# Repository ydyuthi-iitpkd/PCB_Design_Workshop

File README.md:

# PCB_Design_Workshop
PCB Design Workshop Conducted by Y-Dyuthi Club IITPKD

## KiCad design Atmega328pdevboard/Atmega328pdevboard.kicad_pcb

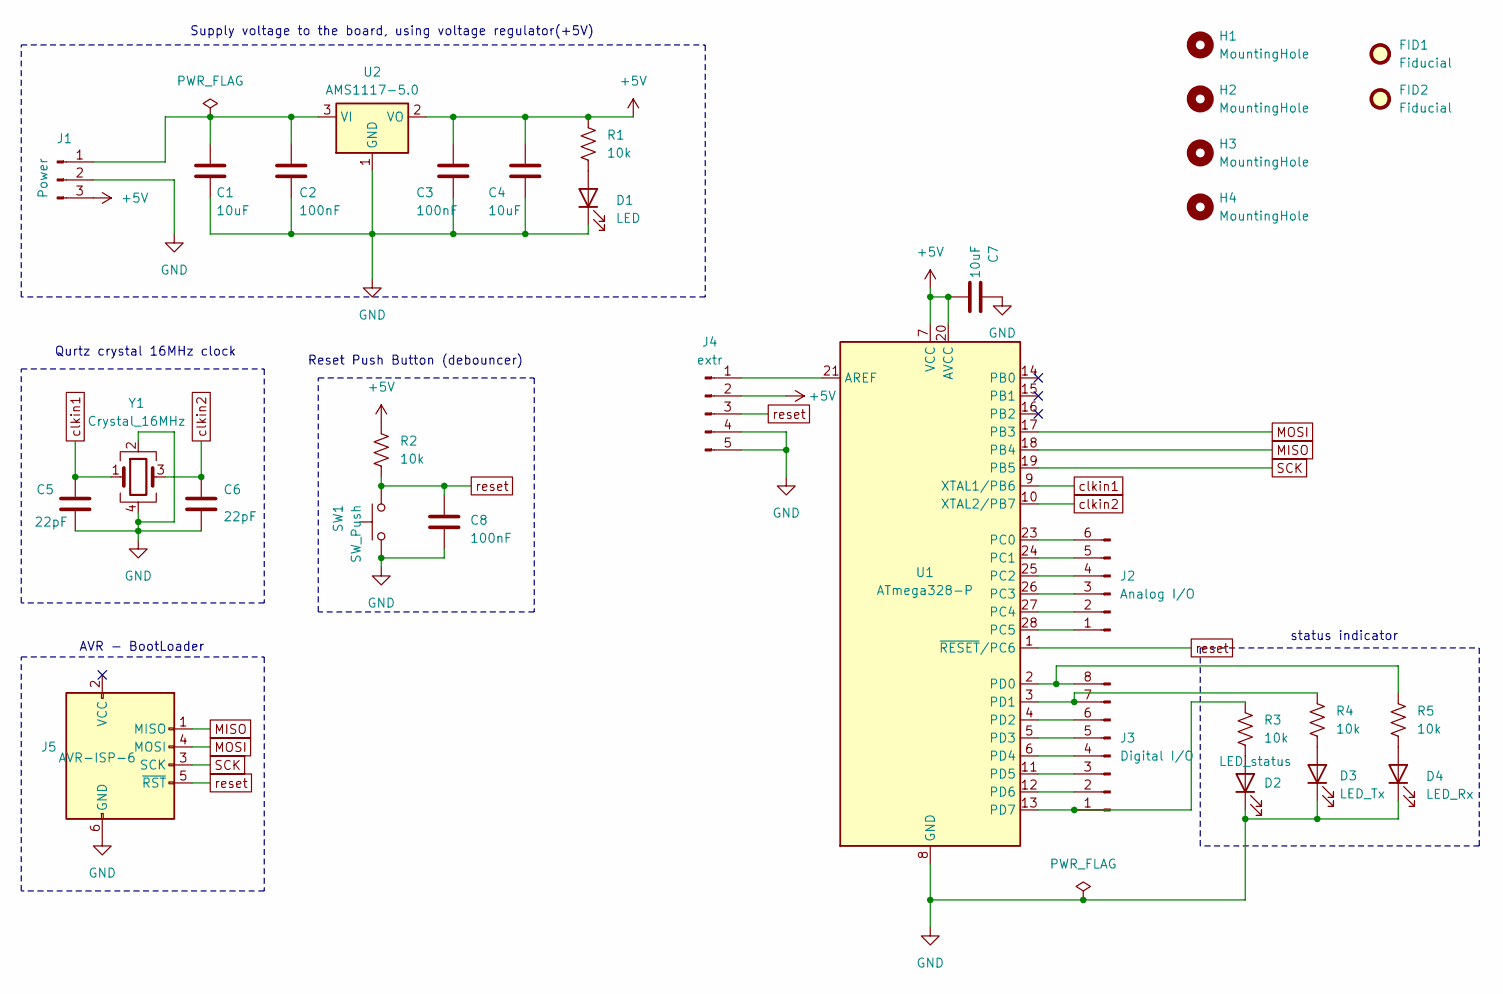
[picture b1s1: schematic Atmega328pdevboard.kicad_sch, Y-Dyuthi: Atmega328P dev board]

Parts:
C1, C4, C7: 10uF; C_0805_2012Metric
C2, C3, C8: 100nF; C_0805_2012Metric
C5, C6: 22pF; C_0402_1005Metric
D1: LED; LED_0805_2012Metric
D2: LED_status; LED_0805_2012Metric
D3: LED_Tx; LED_0805_2012Metric
D4: LED_Rx; LED_0805_2012Metric
FID1, FID2: Fiducial; Fiducial_0.5mm_Mask1.5mm
H1, H2, H3, H4: MountingHole; MountingHole_2.1mm
J1: Power; PinHeader_1x03_P1.27mm_Vertical
J2: Analog I/O; PinSocket_1x06_P1.27mm_Vertical
J3: Digital I/O; PinSocket_1x08_P1.27mm_Vertical
J4: extr; PinSocket_1x05_P1.27mm_Vertical
J5: AVR-ISP-6; PinHeader_2x03_P1.27mm_Vertical
R1, R2, R3, R4, R5: 10k; R_0805_2012Metric
SW1: SW_Push; SW_PUSH_6mm
U1: ATmega328-P; DIP-28_W7.62mm
U2: AMS1117-5.0; SOT-223-3_TabPin2
Y1: Crystal_16MHz; Crystal_SMD_0603-4Pin_6.0x3.5mm

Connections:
+5V: C3.1, C4.1, C7.2, J1.3, J4.2, R1.2, R2.2, U1.7 (VCC), U1.20 (AVCC), U2.2 (VO)
GND: C1.2, C2.2, C3.2, C4.2, C5.2, C6.2, C7.1, C8.2, D1.1 (K), D2.1 (K), D3.1 (K), D4.1 (K), J1.2, J4.4, J4.5, J5.6 (GND), SW1.1, U1.8 (GND), U1.22 (GND), U2.1 (GND), Y1.2, Y1.4
MISO: J5.1 (MISO), U1.18 (PB4)
MOSI: J5.4 (MOSI), U1.17 (PB3)
unnamed: D1.2 (A), R1.1
unnamed: D2.2 (A), R3.1
unnamed: D3.2 (A), R4.1
unnamed: D4.2 (A), R5.1
unnamed: C1.1, C2.1, J1.1, U2.3 (VI)
unnamed: J2.1, U1.28 (PC5)
unnamed: J2.2, U1.27 (PC4)
unnamed: J2.3, U1.26 (PC3)
unnamed: J2.4, U1.25 (PC2)
unnamed: J2.5, U1.24 (PC1)
unnamed: J2.6, U1.23 (PC0)
unnamed: J3.1, R3.2, U1.13 (PD7)
unnamed: J3.2, U1.12 (PD6)
unnamed: J3.3, U1.11 (PD5)
unnamed: J3.4, U1.6 (PD4)
unnamed: J3.5, U1.5 (PD3)
unnamed: J3.6, U1.4 (PD2)
unnamed: J3.7, R4.2, U1.3 (PD1)
unnamed: J3.8, R5.2, U1.2 (PD0)
unnamed: J4.1, U1.21 (AREF)
SCK: J5.3 (SCK), U1.19 (PB5)
clkin1: C5.1, U1.9 (XTAL1/PB6), Y1.1
clkin2: C6.1, U1.10 (XTAL2/PB7), Y1.3
reset: C8.1, J4.3, J5.5 (~RST), R2.1, SW1.2, U1.1 (~RESET/PC6)

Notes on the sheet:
status indicator
Reset Push Button (debouncer)
Qurtz crystal 16MHz clock
AVR - BootLoader
Supply voltage to the board, using voltage regulator(+5V)

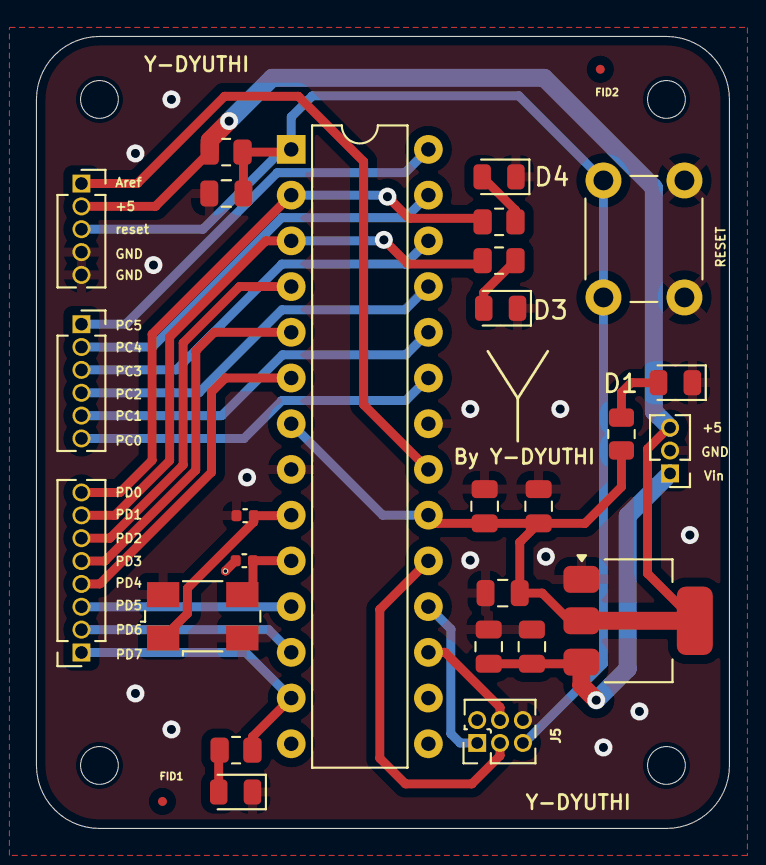
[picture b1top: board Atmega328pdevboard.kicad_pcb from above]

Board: 2 copper layers, 38.5 x 44.0 mm, 32 parts (0 on the bottom side), 28 nets.

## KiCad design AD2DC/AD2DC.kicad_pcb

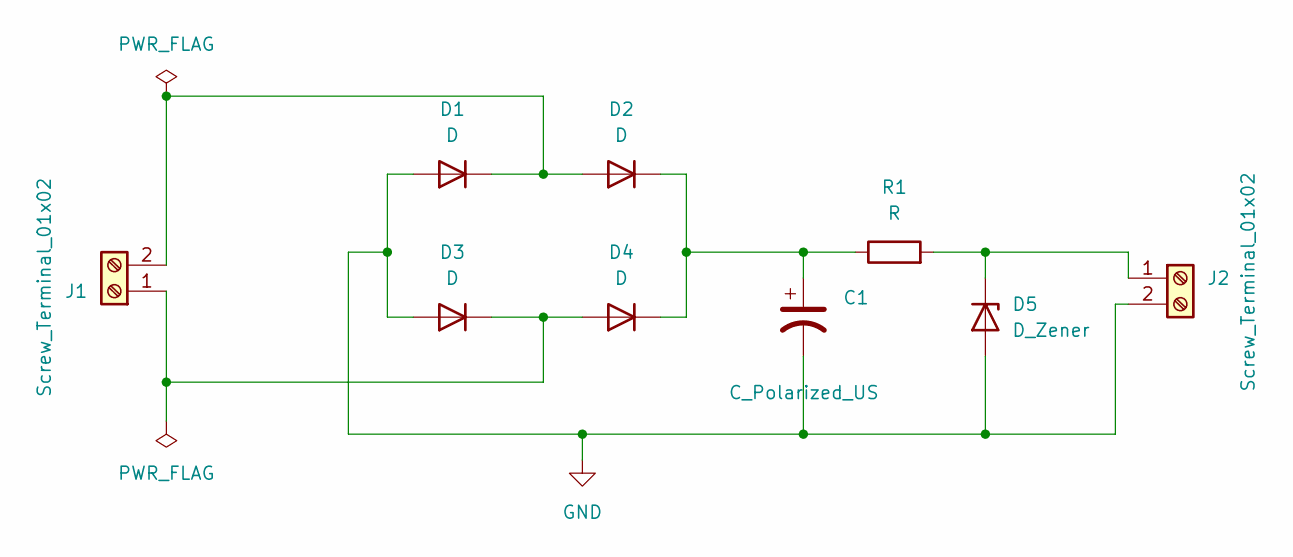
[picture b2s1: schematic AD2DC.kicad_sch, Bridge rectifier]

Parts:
C1: C_Polarized_US; CP_Radial_D10.0mm_P5.00mm
D1, D2, D3, D4: D; D_DO-41_SOD81_P10.16mm_Horizontal
D5: D_Zener; D_A-405_P10.16mm_Horizontal
J1, J2: Screw_Terminal_01x02; TerminalBlock_MetzConnect_Type101_RT01602HBWC_1x02_P5.08mm_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
R1: R; R_Axial_DIN0309_L9.0mm_D3.2mm_P12.70mm_Horizontal

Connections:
GND: C1.2, D1.2 (A), D3.2 (A), D5.2 (A), J2.2
unnamed: D1.1 (K), D2.2 (A), J1.2
unnamed: C1.1, D2.1 (K), D4.1 (K), R1.1
unnamed: D3.1 (K), D4.2 (A), J1.1
unnamed: D5.1 (K), J2.1, R1.2

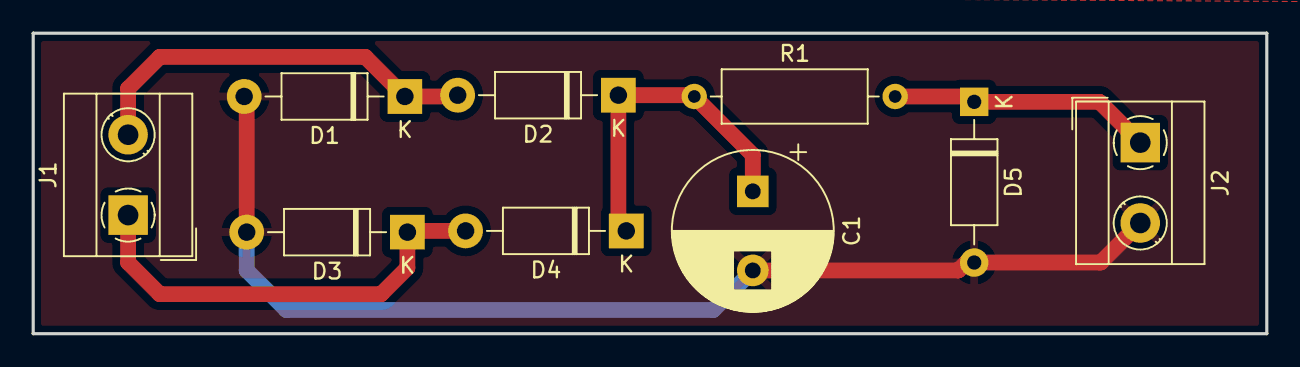
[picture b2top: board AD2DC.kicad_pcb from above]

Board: 2 copper layers, 78.0 x 19.0 mm, 9 parts (0 on the bottom side), 5 nets.

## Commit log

2024-03-28 Adding AD2DC
2024-03-28 Devboard PCB Design
2024-03-28 Workshop PPT
